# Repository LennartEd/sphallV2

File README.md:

# sphallV2

work in progress

## PCB

## CODE

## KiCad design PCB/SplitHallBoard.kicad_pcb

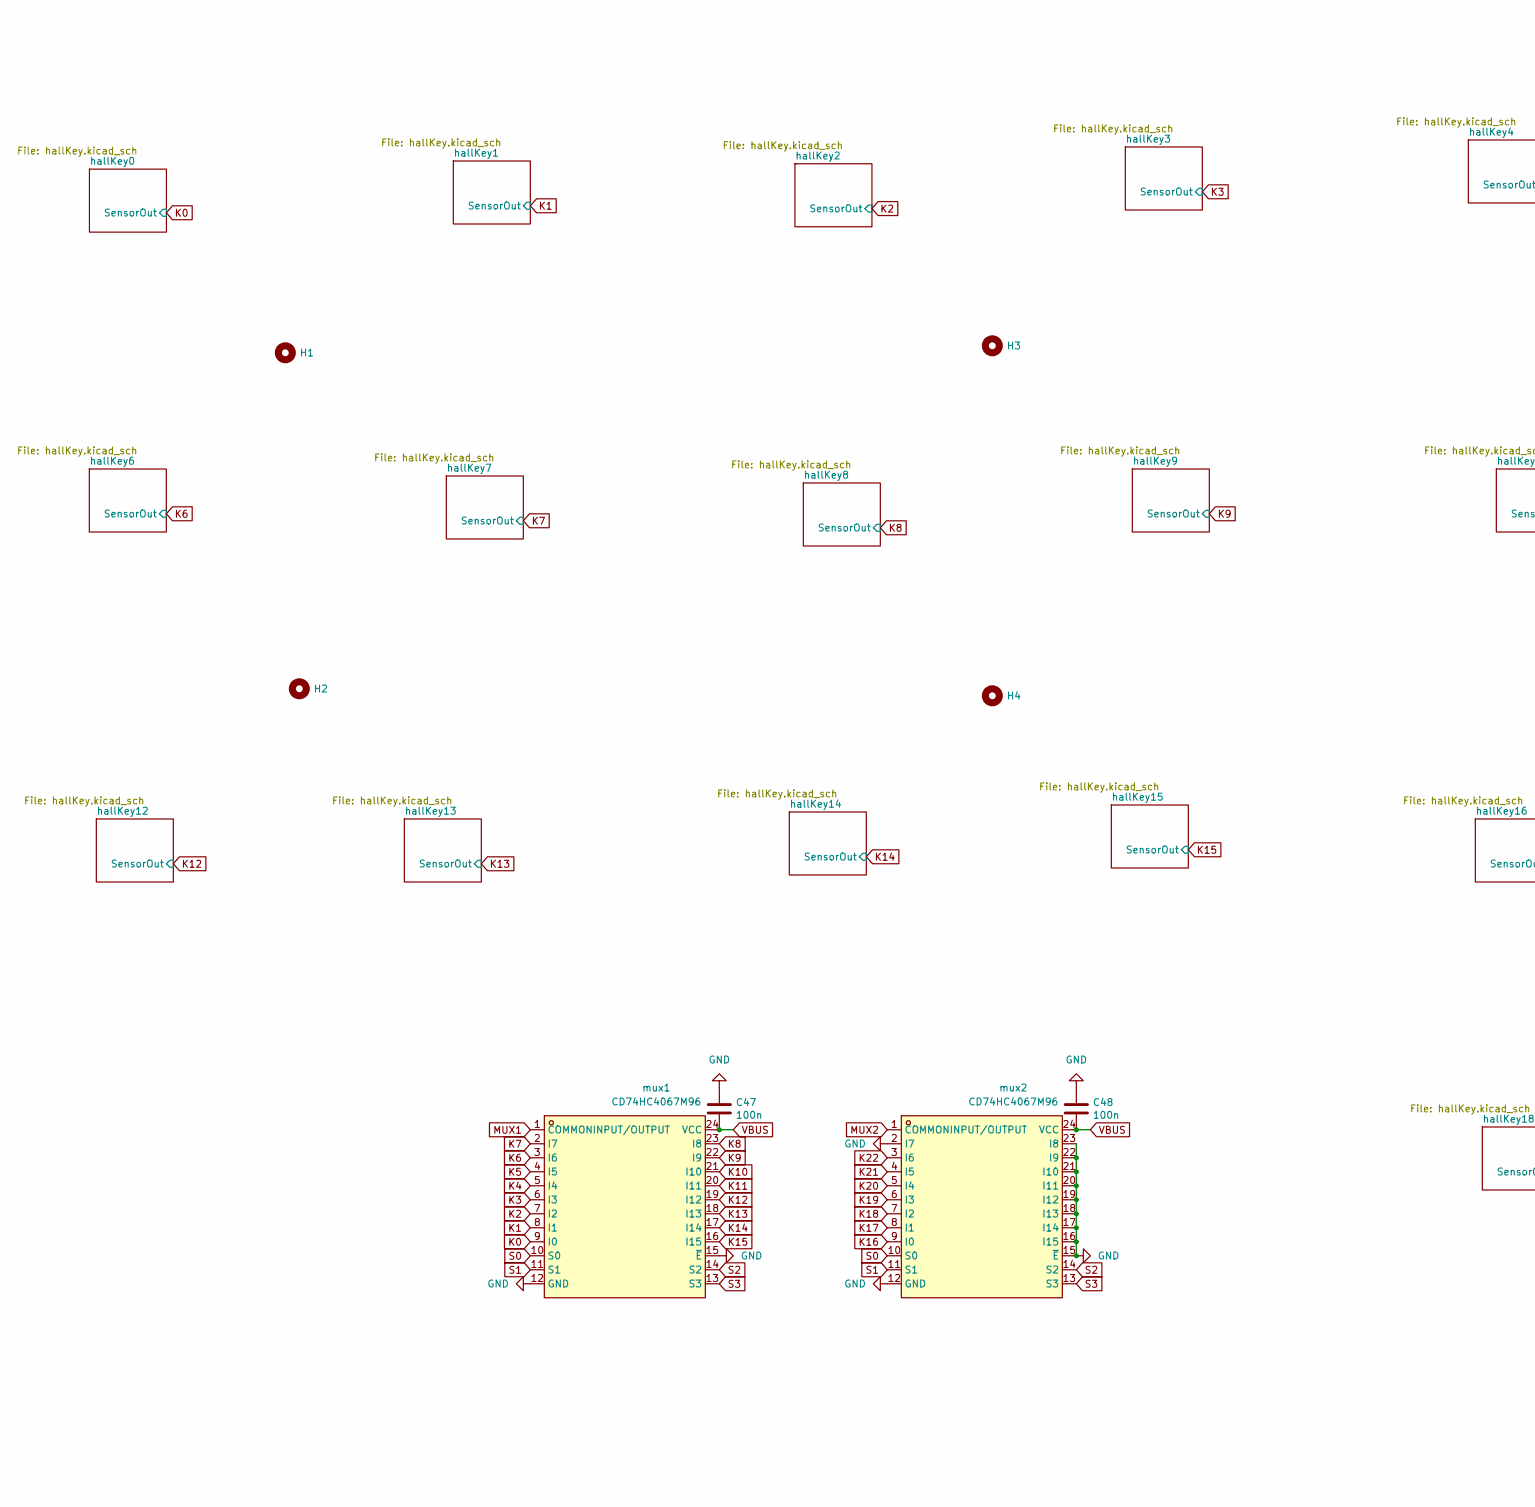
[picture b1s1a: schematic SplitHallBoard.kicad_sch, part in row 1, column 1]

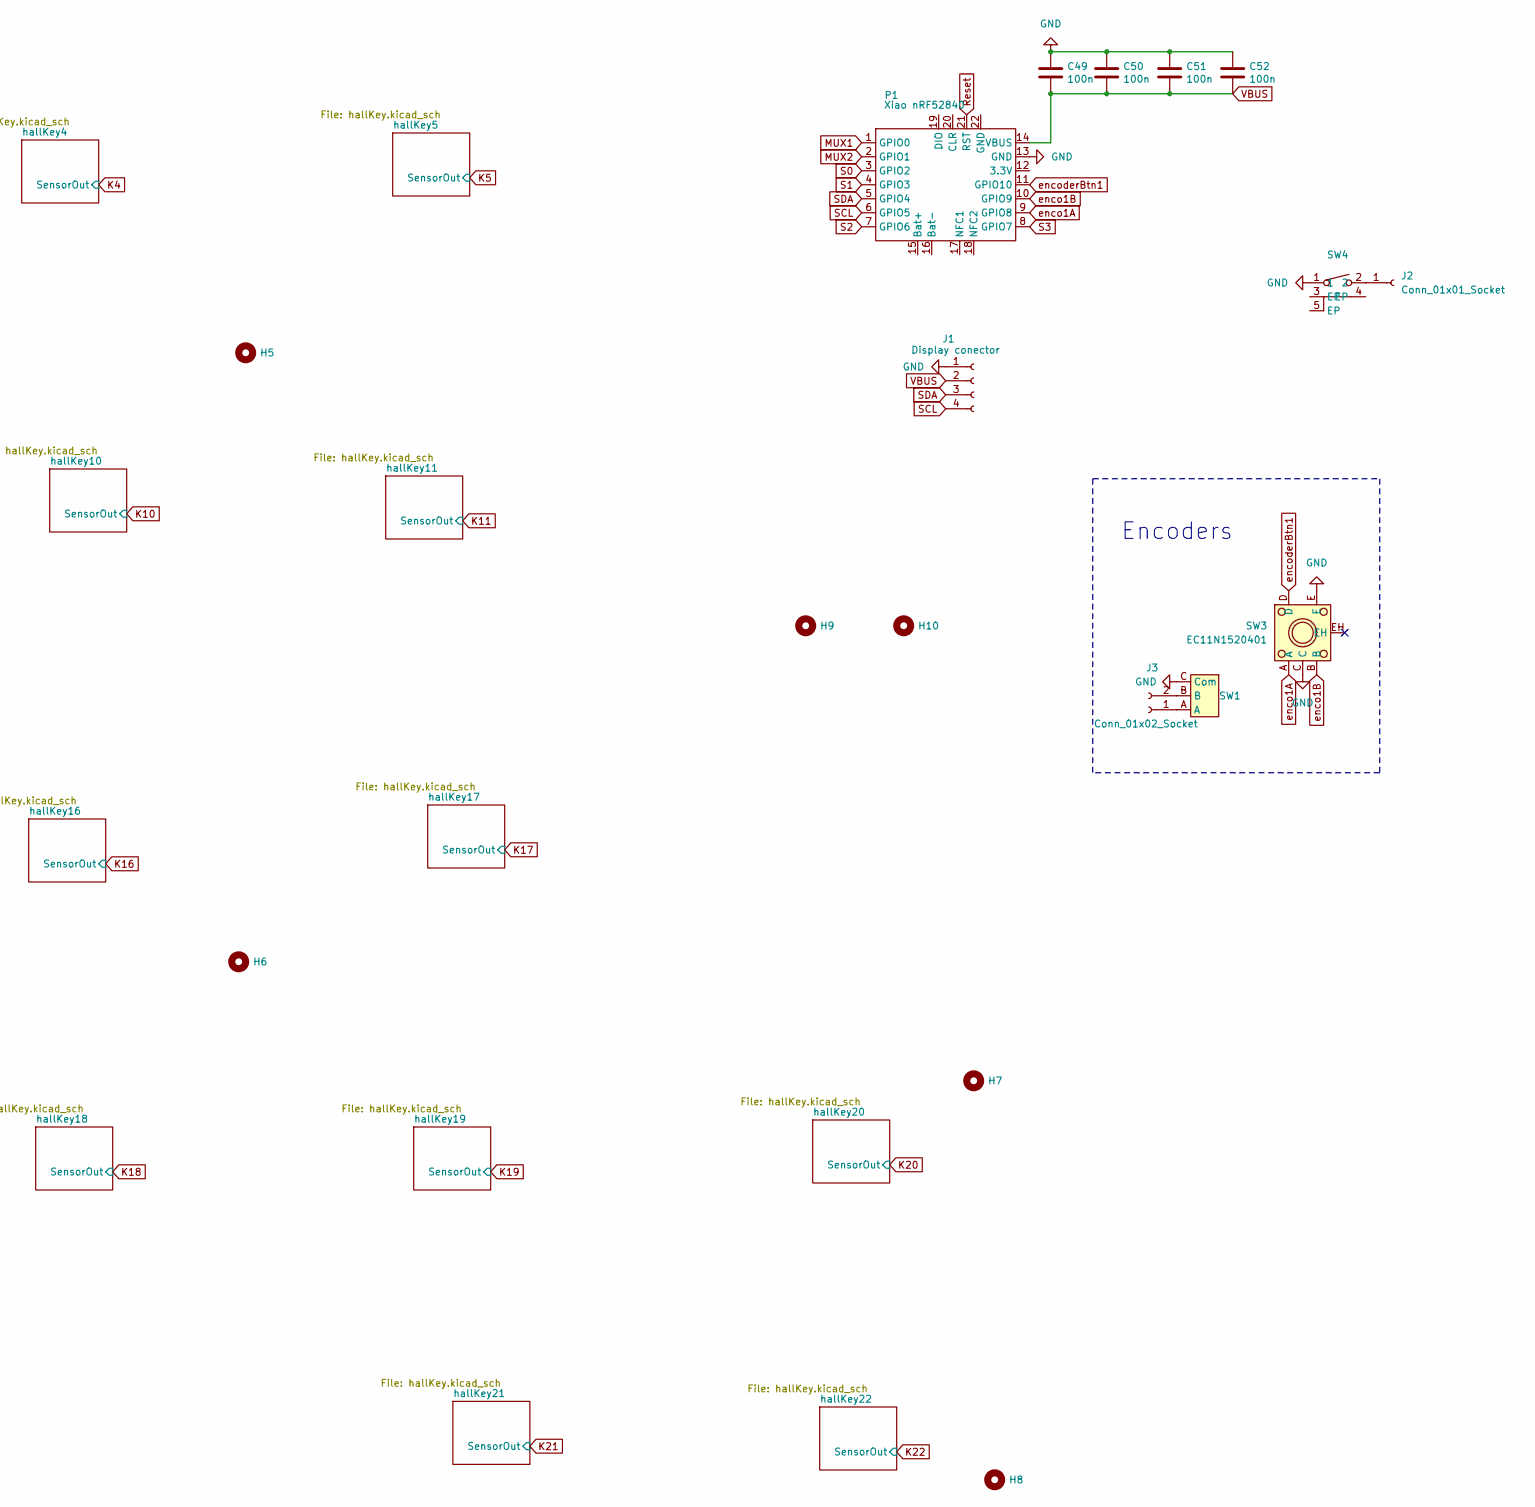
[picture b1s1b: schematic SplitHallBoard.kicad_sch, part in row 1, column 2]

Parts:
C47, C48, C50, C51, C52: 100n; C_0805_2012Metric_Pad1.18x1.45mm_HandSolder; LCSC C1525
C49: 100n; C_0805_2012Metric_Pad1.18x1.45mm_HandSolder; LCSC C52923
H1, H2, H3, H4, H5, H6, H7, H8, H9, H10: MountingHole; MountingHole_2.2mm_M2
J1: Display conector; PinHeader_1x04_P1.00mm_Vertical
J2: Conn_01x01_Socket; PinHeader_1x01_P1.27mm_Vertical
J3: Conn_01x02_Socket; PinHeader_1x02_P1.00mm_Vertical
P1: Xiao nRF52840; XIAO-nRF52840-DIP-Bare
SW1: SW-TH_EC10EXXXXXXX
SW3: EC11N1520401; SW-TH_EC11NXXXX; LCSC Part C470703
SW4: SW-SMD_TCEPQR
mux1, mux2: CD74HC4067M96; SOIC-24_L15.4-W7.5-P1.27-LS10.3-BL; LCSC Part C496123

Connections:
GND: C47.1, C48.1, C49.1, C50.1, C51.1, C52.1, J1.1, P1.13 (GND), SW1.C (Com), SW3.C, SW3.E, SW4.1, mux1.12 (GND), mux1.15 (~E), mux2.2 (I7), mux2.12 (GND), mux2.15 (~E), mux2.16 (I15), mux2.17 (I14), mux2.18 (I13), mux2.19 (I12), mux2.20 (I11), mux2.21 (I10), mux2.22 (I9), mux2.23 (I8); also elsewhere on the board
K0: mux1.9 (I0); also elsewhere on the board
K1: mux1.8 (I1); also elsewhere on the board
K2: mux1.7 (I2); also elsewhere on the board
K3: mux1.6 (I3); also elsewhere on the board
K4: mux1.5 (I4); also elsewhere on the board
K5: mux1.4 (I5); also elsewhere on the board
K6: mux1.3 (I6); also elsewhere on the board
K7: mux1.2 (I7); also elsewhere on the board
K8: mux1.23 (I8); also elsewhere on the board
K9: mux1.22 (I9); also elsewhere on the board
K10: mux1.21 (I10); also elsewhere on the board
K11: mux1.20 (I11); also elsewhere on the board
K12: mux1.19 (I12); also elsewhere on the board
K13: mux1.18 (I13); also elsewhere on the board
K14: mux1.17 (I14); also elsewhere on the board
K15: mux1.16 (I15); also elsewhere on the board
K16: mux2.9 (I0); also elsewhere on the board
K17: mux2.8 (I1); also elsewhere on the board
K18: mux2.7 (I2); also elsewhere on the board
K19: mux2.6 (I3); also elsewhere on the board
K20: mux2.5 (I4); also elsewhere on the board
K21: mux2.4 (I5); also elsewhere on the board
K22: mux2.3 (I6); also elsewhere on the board
MUX1: P1.1 (GPIO0), mux1.1 (COMMONINPUT/OUTPUT)
MUX2: P1.2 (GPIO1), mux2.1 (COMMONINPUT/OUTPUT)
unnamed: J2.1, SW4.2
unnamed: J3.1, SW1.A
unnamed: J3.2, SW1.B
S0: P1.3 (GPIO2), mux1.10 (S0), mux2.10 (S0)
S1: P1.4 (GPIO3), mux1.11 (S1), mux2.11 (S1)
S2: P1.7 (GPIO6), mux1.14 (S2), mux2.14 (S2)
S3: P1.8 (GPIO7), mux1.13 (S3), mux2.13 (S3)
SCL: J1.4, P1.6 (GPIO5)
SDA: J1.3, P1.5 (GPIO4)
VBUS: C47.2, C48.2, C49.2, C50.2, C51.2, C52.2, J1.2, P1.14 (VBUS), mux1.24 (VCC), mux2.24 (VCC); also elsewhere on the board
enco1A: P1.9 (GPIO8), SW3.A
enco1B: P1.10 (GPIO9), SW3.B
encoderBtn1: P1.11 (GPIO10), SW3.D

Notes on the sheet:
Encoders

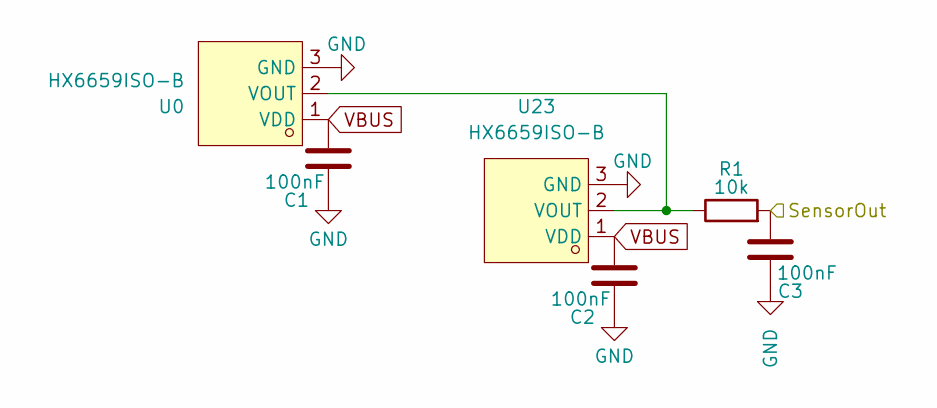
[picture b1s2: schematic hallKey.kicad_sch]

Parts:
C1, C2, C3: 100nF; C_0805_2012Metric_Pad1.18x1.45mm_HandSolder
R1: 10k; R_0805_2012Metric_Pad1.20x1.40mm_HandSolder
U0, U23: HX6659ISO-B; SOT-23-3_L2.9-W1.6-P1.90-LS2.8-BR; LCSC Part C495742

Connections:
GND: C1.2, C2.2, C3.1, U0.3 (GND), U23.3 (GND); also elsewhere on the board
K0: C3.2, R1.2; also elsewhere on the board
unnamed: R1.1, U0.2 (VOUT), U23.2 (VOUT)
VBUS: C1.1, C2.1, U0.1 (VDD), U23.1 (VDD); also elsewhere on the board

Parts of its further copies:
C4, C5, C6, C7, C8, C9, C10, C11, C12, C13, C14, C15, C16, C17, C18, C19, C20, C21, C22, C23, C24, C25, C26, C27, C28, C29, C30, C31, C32, C33, C34, C35, C36, C37, C38, C39, C40, C41, C42, C43, C44, C45, C46, C56, C57, C58, C59, C60, C61, C62, C63, C64, C65, C66, C67, C68, C69, C70, C71, C72, C73, C74, C75, C76, C77, C78: 100nF; C_0805_2012Metric_Pad1.18x1.45mm_HandSolder
R2, R3, R4, R5, R6, R7, R8, R9, R10, R11, R12, R13, R14, R15, R16, R17, R18, R19, R20, R21, R22, R23: 10k; R_0805_2012Metric_Pad1.20x1.40mm_HandSolder
U1, U2, U3, U4, U5, U6, U7, U8, U9, U10, U11, U12, U13, U14, U15, U16, U17, U18, U19, U20, U21, U22, U24, U25, U26, U27, U28, U29, U30, U31, U32, U33, U34, U35, U36, U37, U38, U39, U40, U41, U42, U43, U44, U45: HX6659ISO-B; SOT-23-3_L2.9-W1.6-P1.90-LS2.8-BR; LCSC Part C495742

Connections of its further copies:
GND: C4.2, C5.2, C6.1, C7.2, C8.2, C9.1, C10.2, C11.2, C12.1, C13.2, C14.2, C15.1, C16.2, C17.2, C18.1, C19.2, C20.2, C21.1, C22.2, C23.2, C24.1, C25.2, C26.2, C27.1, C28.2, C29.2, C30.1, C31.2, C32.2, C33.1, C34.2, C35.2, C36.1, C37.2, C38.2, C39.1, C40.2, C41.2, C42.1, C43.2, C44.2, C45.1, C46.2, C56.2, C57.1, C58.2, C59.2, C60.1, C61.2, C62.2, C63.1, C64.2, C65.2, C66.1, C67.2, C68.2, C69.1, C70.2, C71.2, C72.1, C73.2, C74.2, C75.1, C76.2, C77.2, C78.1, U1.3 (GND), U2.3 (GND), U3.3 (GND), U4.3 (GND), U5.3 (GND), U6.3 (GND), U7.3 (GND), U8.3 (GND), U9.3 (GND), U10.3 (GND), U11.3 (GND), U12.3 (GND), U13.3 (GND), U14.3 (GND), U15.3 (GND), U16.3 (GND), U17.3 (GND), U18.3 (GND), U19.3 (GND), U20.3 (GND), U21.3 (GND), U22.3 (GND), U24.3 (GND), U25.3 (GND), U26.3 (GND), U27.3 (GND), U28.3 (GND), U29.3 (GND), U30.3 (GND), U31.3 (GND), U32.3 (GND), U33.3 (GND), U34.3 (GND), U35.3 (GND), U36.3 (GND), U37.3 (GND), U38.3 (GND), U39.3 (GND), U40.3 (GND), U41.3 (GND), U42.3 (GND), U43.3 (GND), U44.3 (GND), U45.3 (GND); also elsewhere on the board
K1: C6.2, R2.2; also elsewhere on the board
K2: C9.2, R3.2; also elsewhere on the board
K3: C12.2, R4.2; also elsewhere on the board
K4: C15.2, R5.2; also elsewhere on the board
K5: C18.2, R6.2; also elsewhere on the board
K6: C21.2, R7.2; also elsewhere on the board
K7: C24.2, R8.2; also elsewhere on the board
K8: C27.2, R9.2; also elsewhere on the board
K9: C30.2, R10.2; also elsewhere on the board
K10: C33.2, R11.2; also elsewhere on the board
K11: C36.2, R12.2; also elsewhere on the board
K12: C39.2, R13.2; also elsewhere on the board
K13: C42.2, R14.2; also elsewhere on the board
K14: C45.2, R15.2; also elsewhere on the board
K15: C57.2, R16.2; also elsewhere on the board
K16: C60.2, R17.2; also elsewhere on the board
K17: C63.2, R18.2; also elsewhere on the board
K18: C66.2, R19.2; also elsewhere on the board
K19: C69.2, R20.2; also elsewhere on the board
K20: C72.2, R21.2; also elsewhere on the board
K21: C75.2, R22.2; also elsewhere on the board
K22: C78.2, R23.2; also elsewhere on the board
unnamed: R2.1, U1.2 (VOUT), U24.2 (VOUT)
unnamed: R3.1, U2.2 (VOUT), U25.2 (VOUT)
unnamed: R11.1, U10.2 (VOUT), U33.2 (VOUT)
unnamed: R12.1, U11.2 (VOUT), U34.2 (VOUT)
unnamed: R13.1, U12.2 (VOUT), U35.2 (VOUT)
unnamed: R14.1, U13.2 (VOUT), U36.2 (VOUT)
unnamed: R15.1, U14.2 (VOUT), U37.2 (VOUT)
unnamed: R16.1, U15.2 (VOUT), U38.2 (VOUT)
unnamed: R17.1, U16.2 (VOUT), U39.2 (VOUT)
unnamed: R18.1, U17.2 (VOUT), U40.2 (VOUT)
unnamed: R19.1, U18.2 (VOUT), U41.2 (VOUT)
unnamed: R20.1, U19.2 (VOUT), U42.2 (VOUT)
unnamed: R21.1, U20.2 (VOUT), U43.2 (VOUT)
unnamed: R22.1, U21.2 (VOUT), U44.2 (VOUT)
unnamed: R23.1, U22.2 (VOUT), U45.2 (VOUT)
unnamed: R4.1, U3.2 (VOUT), U26.2 (VOUT)
unnamed: R5.1, U4.2 (VOUT), U27.2 (VOUT)
unnamed: R6.1, U5.2 (VOUT), U28.2 (VOUT)
unnamed: R7.1, U6.2 (VOUT), U29.2 (VOUT)
unnamed: R8.1, U7.2 (VOUT), U30.2 (VOUT)
unnamed: R9.1, U8.2 (VOUT), U31.2 (VOUT)
unnamed: R10.1, U9.2 (VOUT), U32.2 (VOUT)
VBUS: C4.1, C5.1, C7.1, C8.1, C10.1, C11.1, C13.1, C14.1, C16.1, C17.1, C19.1, C20.1, C22.1, C23.1, C25.1, C26.1, C28.1, C29.1, C31.1, C32.1, C34.1, C35.1, C37.1, C38.1, C40.1, C41.1, C43.1, C44.1, C46.1, C56.1, C58.1, C59.1, C61.1, C62.1, C64.1, C65.1, C67.1, C68.1, C70.1, C71.1, C73.1, C74.1, C76.1, C77.1, U1.1 (VDD), U2.1 (VDD), U3.1 (VDD), U4.1 (VDD), U5.1 (VDD), U6.1 (VDD), U7.1 (VDD), U8.1 (VDD), U9.1 (VDD), U10.1 (VDD), U11.1 (VDD), U12.1 (VDD), U13.1 (VDD), U14.1 (VDD), U15.1 (VDD), U16.1 (VDD), U17.1 (VDD), U18.1 (VDD), U19.1 (VDD), U20.1 (VDD), U21.1 (VDD), U22.1 (VDD), U24.1 (VDD), U25.1 (VDD), U26.1 (VDD), U27.1 (VDD), U28.1 (VDD), U29.1 (VDD), U30.1 (VDD), U31.1 (VDD), U32.1 (VDD), U33.1 (VDD), U34.1 (VDD), U35.1 (VDD), U36.1 (VDD), U37.1 (VDD), U38.1 (VDD), U39.1 (VDD), U40.1 (VDD), U41.1 (VDD), U42.1 (VDD), U43.1 (VDD), U44.1 (VDD), U45.1 (VDD); also elsewhere on the board

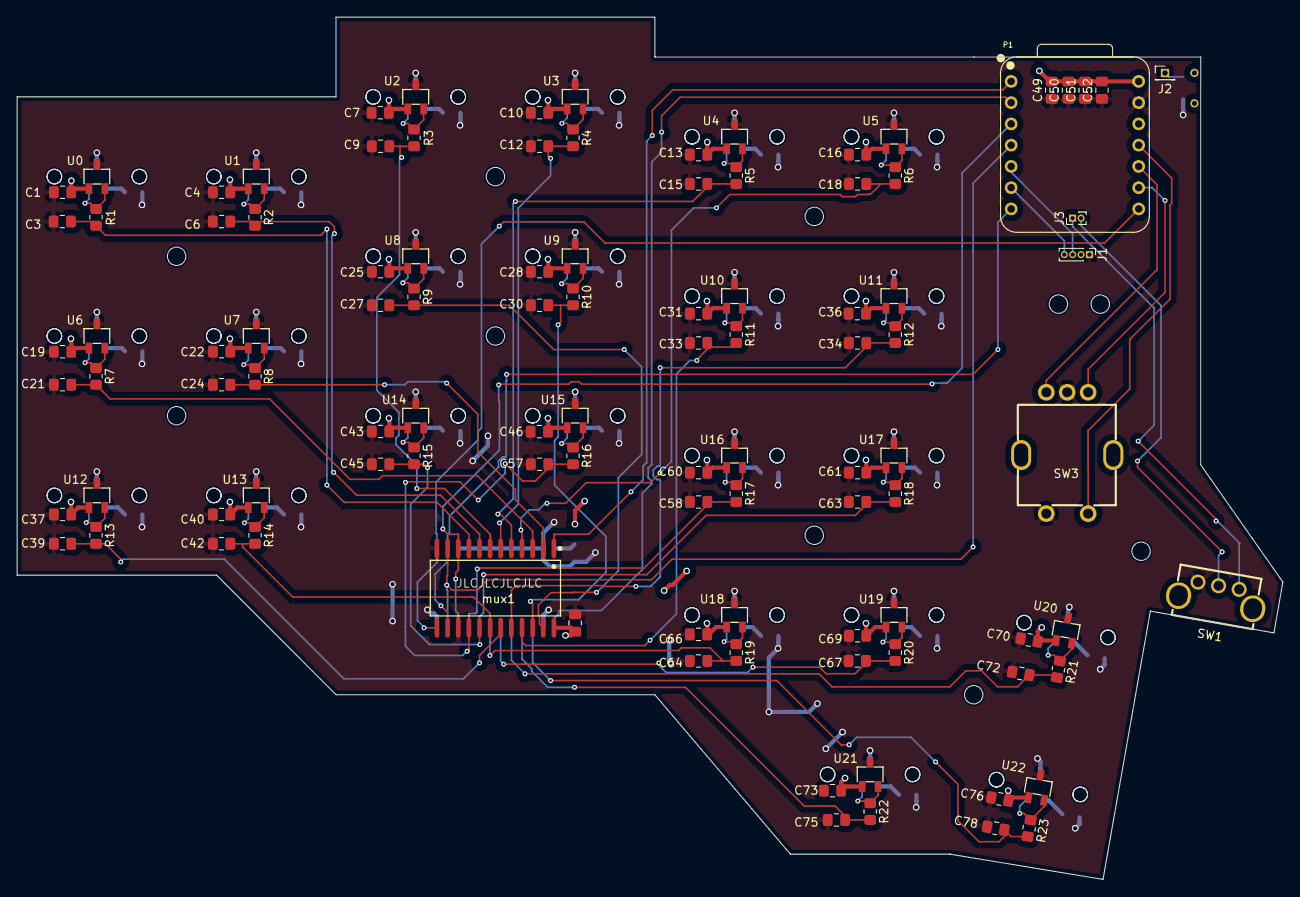
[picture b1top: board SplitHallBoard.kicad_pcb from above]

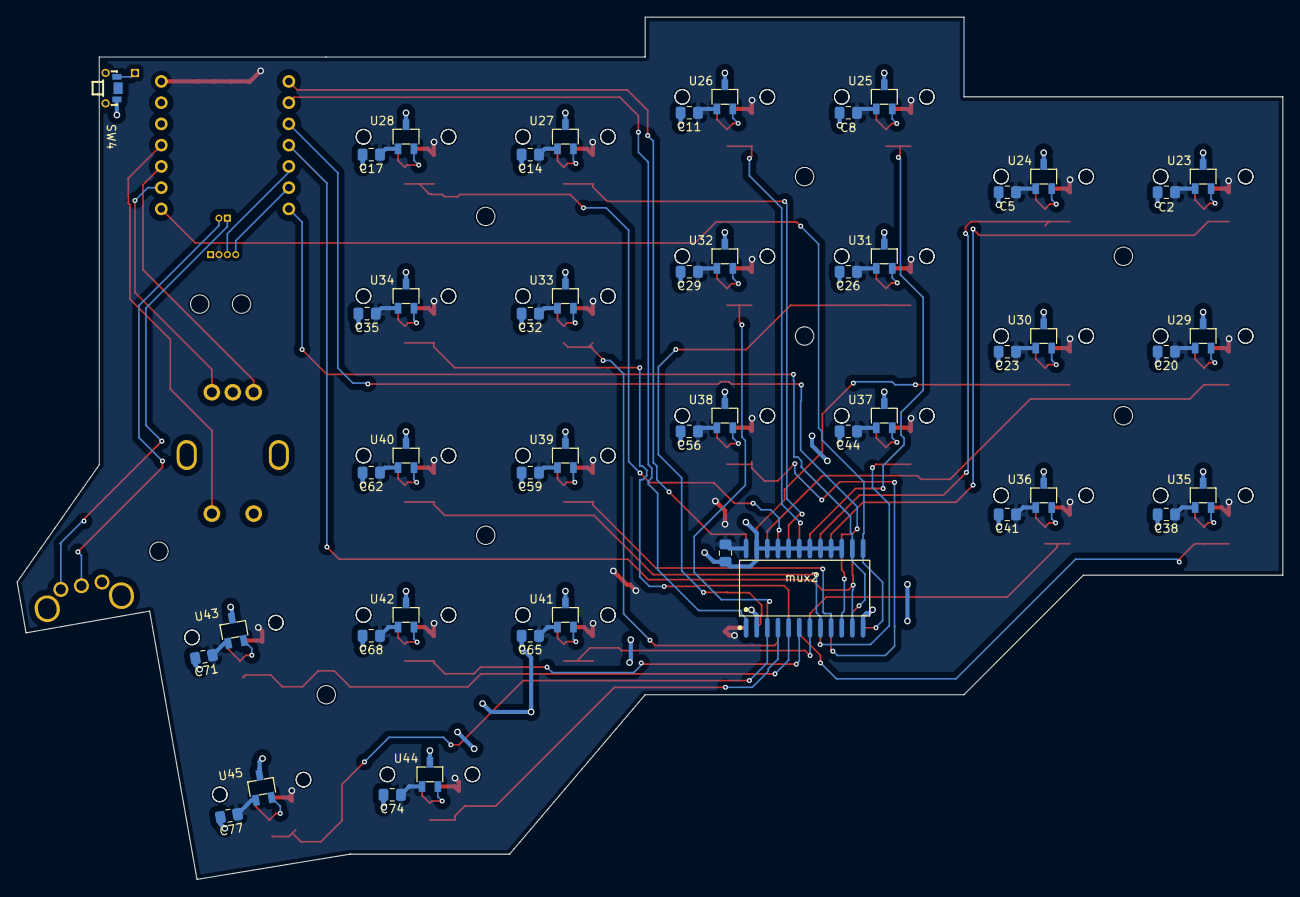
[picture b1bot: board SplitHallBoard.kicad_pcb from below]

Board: 2 copper layers, 151.2 x 103.0 mm, 163 parts (49 on the bottom side), 62 nets.

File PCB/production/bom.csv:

Designator,Footprint,Quantity,Value,LCSC Part #
"C1, C10, C11, C12, C13, C14, C15, C16, C17, C18, C19, C2, C20, C21, C22, C23, C24, C25, C26, C27, C28, C29, C3, C30, C31, C32, C33, C34, C35, C36, C37, C38, C39, C4, C40, C41, C42, C43, C44, C45, C46, C5, C56, C57, C58, C59, C6, C60, C61, C62, C63, C64, C65, C66, C67, C68, C69, C7, C70, C71, C72, C73, C74, C75, C76, C77, C78, C8, C9",0805,69,100nF,
"C47, C48, C50, C51, C52",0805,5,100n,C1525
C49,0805,1,100n,C52923
"H1, H2, H3, H4, H5, H6, H7, H8",MountingHole_2.2mm_M2,8,MountingHole,
J1,PinHeader_1x04_P1.00mm_Vertical,1,Display conector,
J2,PinHeader_1x01_P1.27mm_Vertical,1,Conn_01x01_Socket,
J3,PinHeader_1x02_P1.00mm_Vertical,1,Conn_01x02_Socket,
"MUX1, MUX2",SOIC-24_L15.4-W7.5-P1.27-LS10.3-BL,2,CD74HC4067M96,C496123
P1,XIAO-nRF52840-DIP-Bare,1,Xiao nRF52840,
"R1, R10, R11, R12, R13, R14, R15, R16, R17, R18, R19, R2, R20, R21, R22, R23, R3, R4, R5, R6, R7, R8, R9",0805,23,10k,
SW1,SW-TH_EC10EXXXXXXX,1,~,
SW3,SW-TH_EC11NXXXX,1,EC11N1520401,C470703
SW4,SW-SMD_TCEPQR,1,~,
"U0, U1, U10, U11, U12, U13, U14, U15, U16, U17, U18, U19, U2, U20, U21, U22, U23, U24, U25, U26, U27, U28, U29, U3, U30, U31, U32, U33, U34, U35, U36, U37, U38, U39, U4, U40, U41, U42, U43, U44, U45, U5, U6, U7, U8, U9",SOT-23-3_L2.9-W1.6-P1.90-LS2.8-BR,46,HX6659ISO-B,C495742

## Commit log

2025-04-09 readme update
2025-04-09 readme outline
2025-04-09 pcb added
2025-04-09 cleanup
2025-04-10 changes near mux
2025-04-14 final changes
